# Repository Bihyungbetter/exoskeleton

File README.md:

# Exoskeleton 

## Overview

Exoskeleton is a powered lower-limb exoskeleton with six actuated joints — hip flexion, hip abduction, and knee flexion per leg. Each joint is driven by a CubeMars AK-series actuator (AK70-10 / AK80-64) commanded over CAN by a Teensy 4.1 running through a custom dual-CAN power distribution board, which supplies six independent motor power outputs. The frame — waist, hip abductors, hip-to-thigh, thigh-to-knee, and knee-to-shank sections — is designed in SolidWorks; the electronics are designed in KiCad.

## Features

- Six actuated joints (hip flexion, hip abduction, knee) via CubeMars AK70-10 / AK80-64 actuators
- Custom power distribution board: XT90 main input, 6× XT30 motor power outputs (one per actuator), 50A MIDI fuse, dump resistor, thermal switch input, and battery voltage sense
- Dual CAN bus (CAN A / CAN B, SN65HVD230 transceivers) for actuator communication
- Teensy 4.1 as the main controller
- Modular frame: waist (left/middle/right), hip abductors, hip-to-waist and hip-to-thigh frames, thigh-to-knee frames, knee-to-shank frames, and hip/knee step-up and step-down joint hardware

## Repository layout

- `SolidWorks Assembly/July 2026/July 2026 Exo Assembly/` — SolidWorks parts and the top-level assembly (`Pitt Exo - Final July 2026 Assembly.SLDASM`)
- `pcb/` — KiCad project for the power distribution / control board (schematic, PCB layout, fabrication outputs)
- `pcb/production/` — BOM, designators, placement data, IPC netlist, and Gerber/drill ZIP for fabrication
- `Digikey Order`, `Exoskeleton-JLCPCB Assembly Order (1).xls` — component and assembly ordering records

## Bill of materials

The authoritative electrical BOM is [`pcb/production/bom.csv`](pcb/production/bom.csv). In summary, the power/control board uses:

- 1 Teensy 4.1 controller
- 2 SN65HVD230 CAN transceivers (CAN A / CAN B)
- 1 XT90 power input and 6 XT30 motor power connectors
- 1 50A MIDI fuse, 1 IRFB4110 MOSFET, dump resistor output, thermal switch input, and battery sense header
- Supporting passives (bulk 680 µF caps, TVS/flyback diodes, 120 Ω CAN bus termination)

The mechanical assembly (SolidWorks) is built from 22 parts, including the waist sections, left/right hip abductors, hip-to-waist and hip-to-thigh frames, thigh-to-knee and knee-to-shank frames, hip/knee step-up and step-down joint hardware, and the AK70-10 / AK80-64 motor body and center mounts.

## Pictures

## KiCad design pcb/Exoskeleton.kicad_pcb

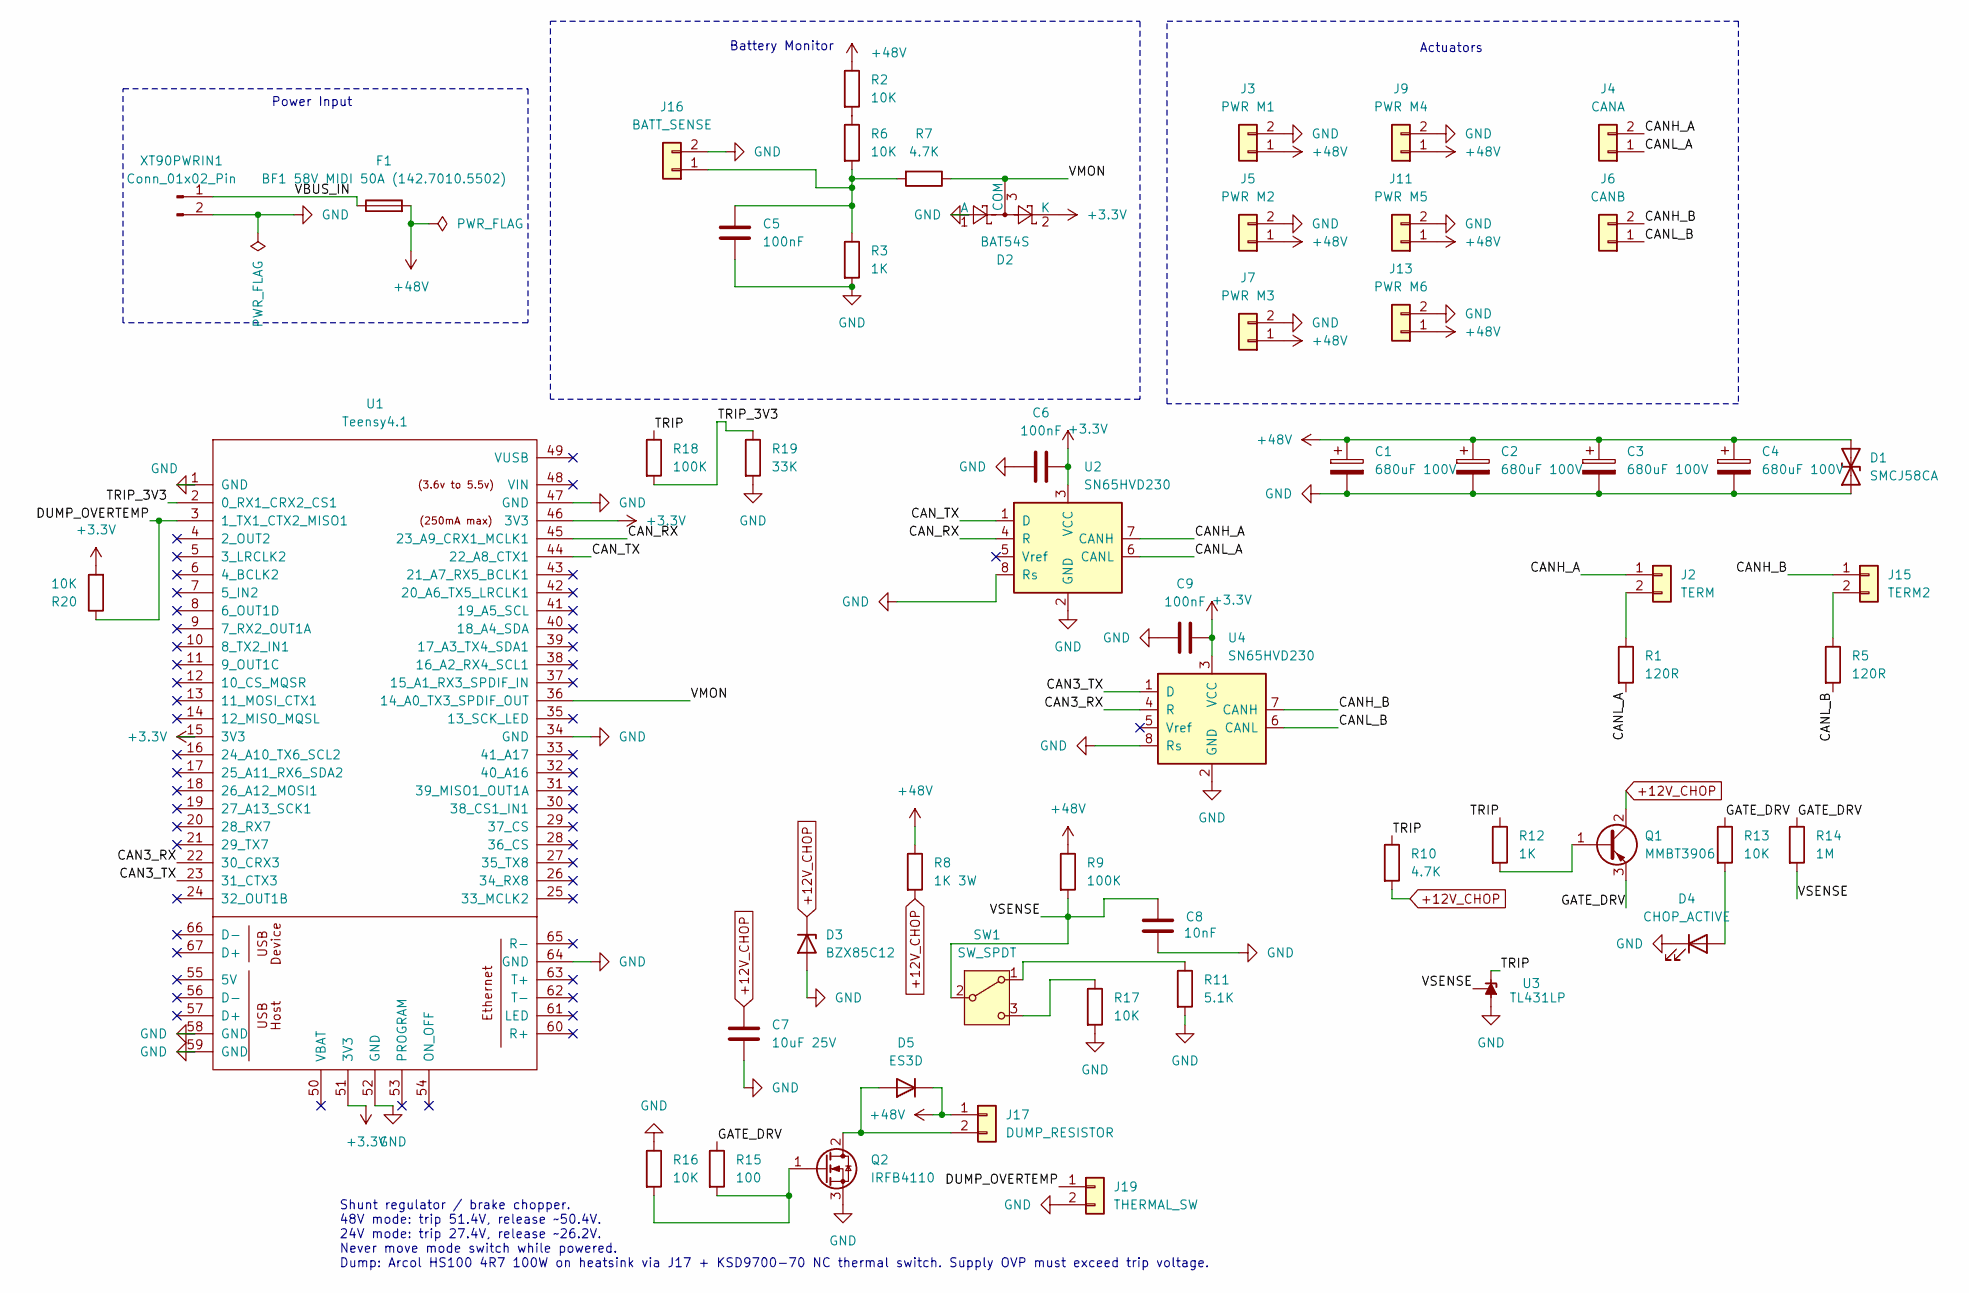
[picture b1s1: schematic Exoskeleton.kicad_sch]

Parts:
C1, C2, C3, C4: 680uF 100V; CP_Radial_D18.0mm_P7.50mm
C5: 100nF; C_Disc_D7.5mm_W4.4mm_P5.00mm
C6, C9: 100nF; C_0805_2012Metric
C7: 10uF 25V; C_1206_3216Metric
C8: 10nF; C_0805_2012Metric
D1: SMCJ58CA; D_SMC
D2: BAT54S; SOT-23
D3: BZX85C12; D_DO-41_SOD81_P10.16mm_Horizontal
D4: CHOP_ACTIVE; LED_D3.0mm
D5: ES3D; D_SMC
F1: BF1 58V MIDI 50A (142.7010.5502); Fuse_MIDI_BF1-58V_50A_BoltDown_2xM6_P30mm
J2: TERM; PinHeader_1x02_P2.54mm_Vertical
J3: PWR M1; AMASS_XT30PW-F_1x02_P2.50mm_Horizontal
J4: CANA; JST_GH_SM02B-GHS-TB_1x02-1MP_P1.25mm_Horizontal
J5: PWR M2; AMASS_XT30PW-F_1x02_P2.50mm_Horizontal
J6: CANB; JST_GH_SM02B-GHS-TB_1x02-1MP_P1.25mm_Horizontal
J7: PWR M3; AMASS_XT30PW-F_1x02_P2.50mm_Horizontal
J9: PWR M4; AMASS_XT30PW-F_1x02_P2.50mm_Horizontal
J11: PWR M5; AMASS_XT30PW-F_1x02_P2.50mm_Horizontal
J13: PWR M6; AMASS_XT30PW-F_1x02_P2.50mm_Horizontal
J15: TERM2; PinHeader_1x02_P2.54mm_Vertical
J16: BATT_SENSE; PinHeader_1x02_P2.54mm_Vertical
J17: DUMP_RESISTOR; AMASS_XT30PW-F_1x02_P2.50mm_Horizontal
J19: THERMAL_SW; PinHeader_1x02_P2.54mm_Vertical
Q1: MMBT3906; SOT-23
Q2: IRFB4110; TO-220-3_Vertical
R1, R5: 120R; R_Axial_DIN0207_L6.3mm_D2.5mm_P10.16mm_Horizontal
R2, R6, R13, R16, R17, R20: 10K; R_0805_2012Metric
R3: 1K; R_Axial_DIN0207_L6.3mm_D2.5mm_P10.16mm_Horizontal
R7, R10: 4.7K; R_0805_2012Metric
R8: 1K 3W; R_Axial_Power_L20.0mm_W6.4mm_P25.40mm
R9, R18: 100K; R_0805_2012Metric
R11: 5.1K; R_0805_2012Metric
R12: 1K; R_0805_2012Metric
R14: 1M; R_0805_2012Metric
R15: 100; R_0805_2012Metric
R19: 33K; R_0805_2012Metric
SW1: SW_SPDT; SW_Slide_SPDT_Straight_CK_OS102011MS2Q
U1: Teensy4.1; Teensy41
U2, U4: SN65HVD230; SOIC-8_3.9x4.9mm_P1.27mm
U3: TL431LP; TO-92_Inline
XT90PWRIN1: Conn_01x02_Pin; AMASS_XT90PW-M_1x02_P10.90mm_Horizontal

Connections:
+3.3V: C6.2, C9.2, D2.2 (K), R20.2, U1.15 (3V3), U1.46 (3V3), U1.51 (3V3), U2.3 (VCC), U4.3 (VCC)
+12V_CHOP: C7.1, D3.1 (K), Q1.2 (C), R8.2, R10.2
+48V: C1.1, C2.1, C3.1, C4.1, D1.2 (A2), D5.1 (K), F1.2, J3.1, J5.1, J7.1, J9.1, J11.1, J13.1, J17.1, R2.1, R8.1, R9.1
/CAN3_RX: U1.22 (30_CRX3), U4.4 (R)
/CAN3_TX: U1.23 (31_CTX3), U4.1 (D)
/CANH_A: J2.1, J4.2, U2.7 (CANH)
/CANH_B: J6.2, J15.1
/CANH_B: U4.7 (CANH)
/CANL_A: J4.1, R1.2, U2.6 (CANL)
/CANL_B: J6.1, R5.2, U4.6 (CANL)
/CAN_RX: U1.45 (23_A9_CRX1_MCLK1), U2.4 (R)
/CAN_TX: U1.44 (22_A8_CTX1), U2.1 (D)
/DUMP_OVERTEMP: J19.1, R20.1, U1.3 (1_TX1_CTX2_MISO1)
/GATE_DRV: Q1.3 (E), R13.1, R14.1, R15.1
/TRIP: R10.1, R12.1, R18.1, U3.3 (K)
/TRIP_3V3: R18.2, R19.1, U1.2 (0_RX1_CRX2_CS1)
/VBUS_IN: F1.1, XT90PWRIN1.1
/VMON: D2.3 (COM), R7.1, U1.36 (14_A0_TX3_SPDIF_OUT)
/VSENSE: C8.1, R9.2, R14.2, SW1.2 (B), U3.1 (REF)
GND: C1.2, C2.2, C3.2, C4.2, C5.2, C6.1, C7.2, C8.2, C9.1, D1.1 (A1), D2.1 (A), D3.2 (A), D4.1 (K), J3.2, J5.2, J7.2, J9.2, J11.2, J13.2, J16.2, J19.2, Q2.3 (S), R3.2, R11.2, R16.1, R17.2, R19.2, U1.1 (GND), U1.34 (GND), U1.47 (GND), U1.52 (GND), U1.58 (GND), U1.59 (GND), U1.64 (GND), U2.2 (GND), U2.8 (Rs), U3.2 (A), U4.2 (GND), U4.8 (Rs), XT90PWRIN1.2
unnamed: D4.2 (A), R13.2
unnamed: D5.2 (A), J17.2, Q2.2 (D)
unnamed: J2.2, R1.1
unnamed: J15.2, R5.1
unnamed: C5.1, J16.1, R3.1, R6.2, R7.2
unnamed: Q1.1 (B), R12.2
unnamed: Q2.1 (G), R15.2, R16.2
unnamed: R2.2, R6.1
unnamed: R11.1, SW1.1 (A)
unnamed: R17.1, SW1.3 (C)

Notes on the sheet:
Actuators
Power Input
Shunt regulator / brake chopper. 48V mode: trip 51.4V, release ~50.4V. 24V mode: trip 27.4V, release ~26.2V. Never move mode switch while powered. Dump: Arcol HS100 4R7 100W on heatsink via J17 + KSD9700-70 NC thermal switch. Supply OVP must exceed trip voltage.
Battery Monitor

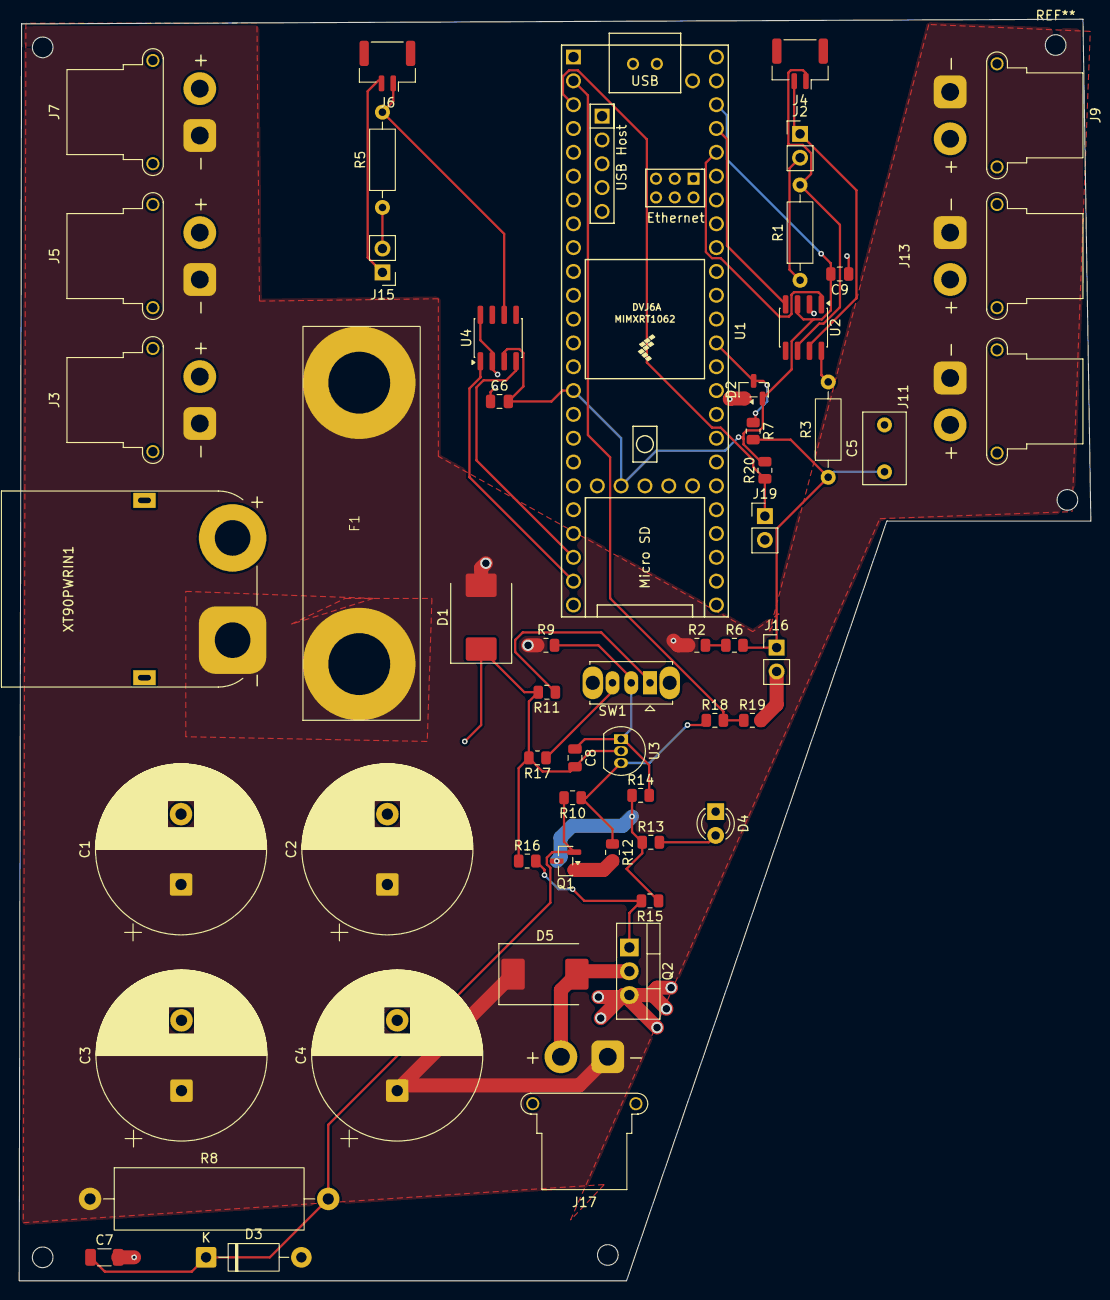
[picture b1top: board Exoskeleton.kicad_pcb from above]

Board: 4 copper layers, 114.2 x 134.5 mm, 55 parts (0 on the bottom side), 29 nets.

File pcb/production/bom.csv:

Designator,Footprint,Quantity,Value,LCSC Part #
"_4, _3, _2, ",,4,,
"C1, C2, C3, C4",CP_Radial_D18.0mm_P7.50mm,4,680uF 100V,
C5,C_Disc_D7.5mm_W4.4mm_P5.00mm,1,100nF,
"C6, C9",0805,2,100nF,
C7,1206,1,10uF 25V,
C8,0805,1,10nF,
D1,D_SMC,1,SMCJ58CA,
D2,SOT-23,1,BAT54S,
D3,D_DO-41_SOD81_P10.16mm_Horizontal,1,BZX85C12,
D4,LED_D3.0mm,1,CHOP_ACTIVE,
D5,D_SMC,1,ES3D,
F1,Fuse_MIDI_BF1-58V_50A_BoltDown_2xM6_P30mm,1,BF1 58V MIDI 50A (142.7010.5502),
J11,AMASS_XT30PW-F_1x02_P2.50mm_Horizontal,1,PWR M5,
J13,AMASS_XT30PW-F_1x02_P2.50mm_Horizontal,1,PWR M6,
J15,PinHeader_1x02_P2.54mm_Vertical,1,TERM2,
J16,PinHeader_1x02_P2.54mm_Vertical,1,BATT_SENSE,
J17,AMASS_XT30PW-F_1x02_P2.50mm_Horizontal,1,DUMP_RESISTOR,
J19,PinHeader_1x02_P2.54mm_Vertical,1,THERMAL_SW,
J2,PinHeader_1x02_P2.54mm_Vertical,1,TERM,
J3,AMASS_XT30PW-F_1x02_P2.50mm_Horizontal,1,PWR M1,
J4,JST_GH_SM02B-GHS-TB_1x02-1MP_P1.25mm_Horizontal,1,CANA,
J5,AMASS_XT30PW-F_1x02_P2.50mm_Horizontal,1,PWR M2,
J6,JST_GH_SM02B-GHS-TB_1x02-1MP_P1.25mm_Horizontal,1,CANB,
J7,AMASS_XT30PW-F_1x02_P2.50mm_Horizontal,1,PWR M3,
J9,AMASS_XT30PW-F_1x02_P2.50mm_Horizontal,1,PWR M4,
Q1,SOT-23,1,MMBT3906,
Q2,TO-220-3_Vertical,1,IRFB4110,
"R1, R5",R_Axial_DIN0207_L6.3mm_D2.5mm_P10.16mm_Horizontal,2,120R,
"R10, R7",0805,2,4.7K,
R11,0805,1,5.1K,
R12,0805,1,1K,
"R13, R16, R17, R2, R20, R6",0805,6,10K,
R14,0805,1,1M,
R15,0805,1,100,
"R18, R9",0805,2,100K,
R19,0805,1,33K,
R3,R_Axial_DIN0207_L6.3mm_D2.5mm_P10.16mm_Horizontal,1,1K,
R8,R_Axial_Power_L20.0mm_W6.4mm_P25.40mm,1,1K 3W,
SW1,SW_Slide_SPDT_Straight_CK_OS102011MS2Q,1,SW_SPDT,
U1,Teensy41,1,Teensy4.1,
"U2, U4",SOIC-8_3.9x4.9mm_P1.27mm,2,SN65HVD230,
U3,TO-92_Inline,1,TL431LP,
XT90PWRIN1,AMASS_XT90PW-M_1x02_P10.90mm_Horizontal,1,Conn_01x02_Pin,
